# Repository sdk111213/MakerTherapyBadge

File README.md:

# MakerTherapyBadge
This repository is for the Electronics Pro Milestone at Purdue University for Spring 2021
This project will be a Maker therapy badge - a handheld electronic device that toggles through different settings for moods and even has an option for some games.

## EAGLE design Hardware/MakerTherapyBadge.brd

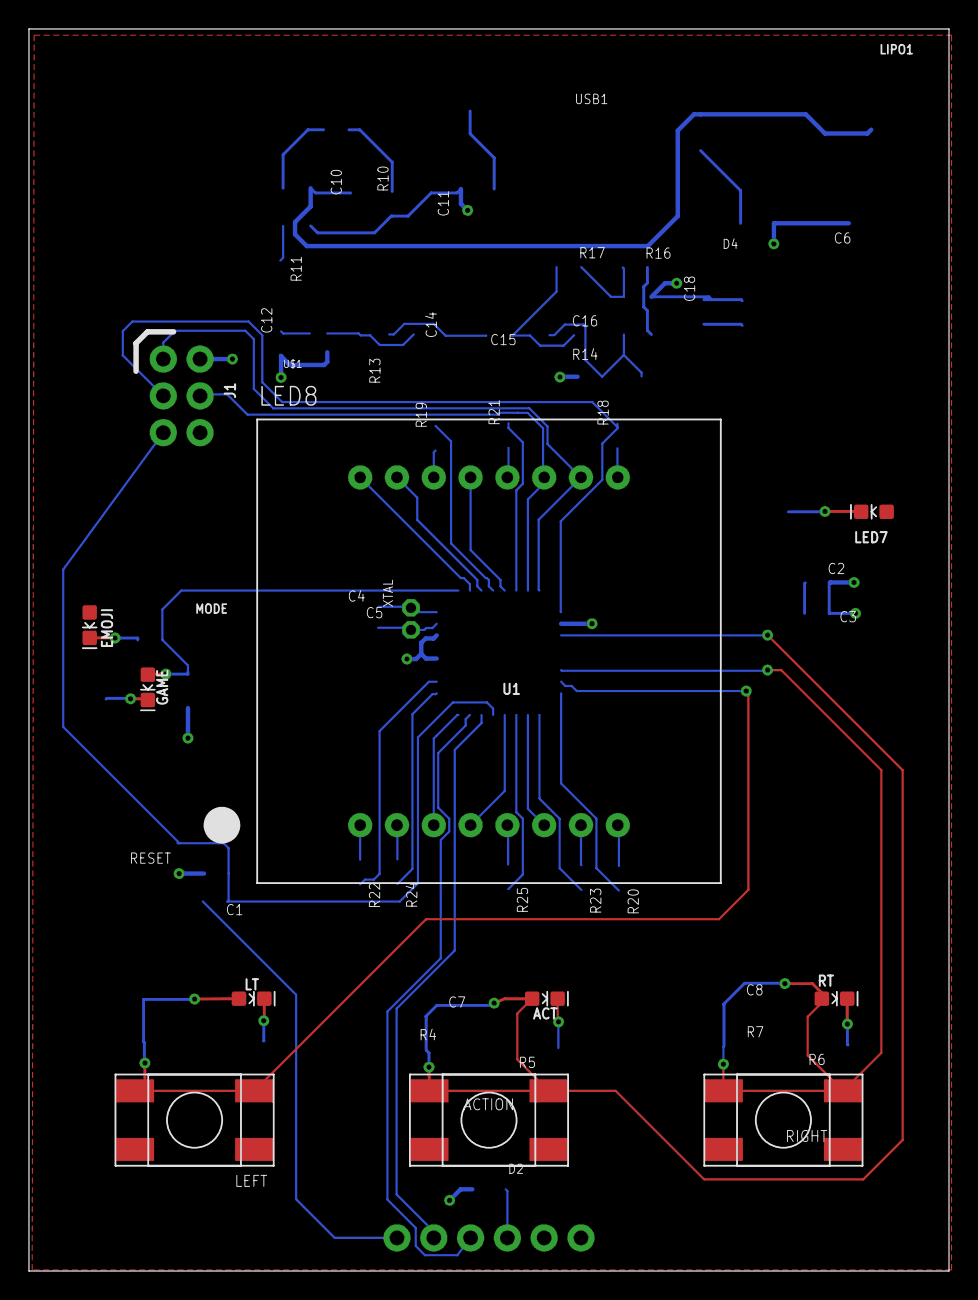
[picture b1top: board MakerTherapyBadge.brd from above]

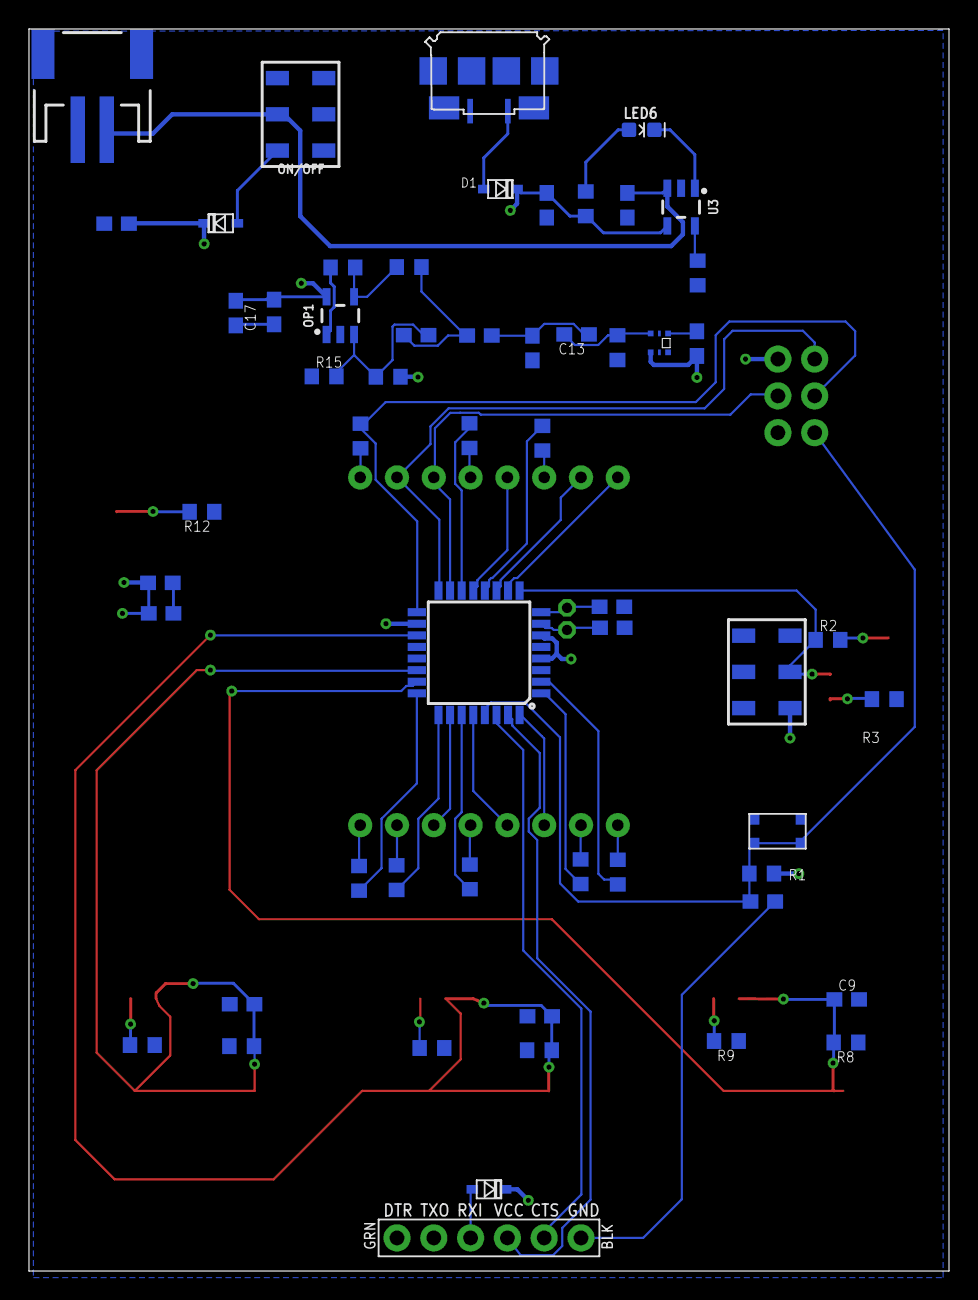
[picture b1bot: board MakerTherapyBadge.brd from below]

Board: 2 copper layers, 63.5 x 85.7 mm, 69 parts (57 on the bottom side), 55 nets.

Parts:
ACT: LED-0603
ACTION: SPST.KT11P4SM34LFS
C1, C3: 0.1u; C0603
C2, C16: 2.2u; C0603
C4, C5: 22p; C0603
C6, C10, C13, C14, C15: 4.7u; C0603
C7, C8, C9, C12, C17: 100n; C0603
C11: C0603
C18: 1u; C0603
D1, D4: 1A/23V/620mV; USC
D2: USC
EMOJI: LED-0603
FTDI1: FTDI_DEVICE
GAME: LED-0603
J1: AVR_SPI_PROG_3X2NS; 2X3-NS
LED6, LED7: LED-0603
LED8: SEGMENT_BL-M12A881UR
LEFT: SPST.KT11P4SM34LFS
LIPO1: JST-2-SMD
LT: LED-0603
MODE: SWITCH.JS202011JXQNUPWARDS; SWITCH.00
ON/OFF: SWITCH.JS202011JXQNUPWARDS; SWITCH.00
OP1: SOT23-5
R1, R4, R7, R8, R11, R17: 10k; R0603
R2, R3, R5, R6, R9, R10: 1k; R0603
R12: 487; R0603
R13: 12k; R0603
R14, R15: 210k; R0603
R16: 3.3M; R0603
R18, R19, R20, R21, R22, R23, R24, R25: 205; R0603
RESET: BUTTON-GULLWING
RIGHT: SPST.KT11P4SM34LFS
RT: LED-0603
U1: ATMEGA328P_TQFP; TQFP32-08
U3: MCP73831.SOT23-5; SOT23-5
U$1: ADPS9008; 6-PIN.CHIPLED
USB1: USB.MICRO.PWR-BIGGERPADS; USB-MICRO-01.BIGGERPADS.PWR
XTAL: CA-301

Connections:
ACTION: ACT.A, ACTION.3, ACTION.4, C7.2, R4.2, U1.19
DTR: C1.2, FTDI1.GND
GND: C2.2, C3.2, C4.2, C5.2, C6.2, C7.1, C8.1, C9.2, C10.2, C11.2, C12.1, C14.2, C17.2, C18.2, FTDI1.DTR, FTDI1.TXO, J1.6, LIPO1.1, MODE.1, OP1.2, R3.1, R4.1, R5.1, R6.1, R7.1, R8.1, R9.1, R11.1, R12.1, R13.1, R15.1, RESET.3, RESET.4, U1.3, U1.5, U1.21, U3.2, U$1.4, USB1.5
LD1: R22.1, U1.2
LD2: R24.1, U1.1
LD3: LED8.3, U1.32
LD4: LED8.4, U1.28
LD5: R25.1, U1.27
LD6: LED8.6, U1.26
LD7: R23.1, U1.25
LD8: R20.1, U1.24
LD9: J1.3, R18.1, U1.17
LD10: J1.1, LED8.10, U1.16
LD11: J1.4, LED8.11, U1.15
LD12: R21.1, U1.14
LD13: LED8.13, U1.13
LD14: R19.1, U1.12
LD15: LED8.15, U1.11
LD16: LED8.16, U1.10
LEFT: C9.1, LEFT.3, LEFT.4, LT.A, R8.2, U1.23
MODE: GAME.A, MODE.2, R2.1, U1.9
unnamed: LED8.9, R18.2
unnamed: D2.+, FTDI1.RXI
unnamed: LED8.14, R19.2
unnamed: LED8.8, R20.2
unnamed: LED8.12, R21.2
unnamed: C4.1, U1.8, XTAL.1
unnamed: D4.+, ON/OFF.1
unnamed: EMOJI.C, R2.2
unnamed: C5.1, U1.7, XTAL.2
unnamed: LT.C, R9.2
unnamed: LED8.1, R22.2
unnamed: LED8.7, R23.2
unnamed: LED8.2, R24.2
unnamed: GAME.C, R3.2
unnamed: ACT.C, R5.2
unnamed: R6.2, RT.C
unnamed: D1.+, USB1.1
unnamed: LED6.A, R10.1
unnamed: LED8.5, R25.2
unnamed: LED7.C, R12.2
unnamed: R11.2, U3.5
unnamed: OP1.4, R16.2, R17.1
unnamed: C16.2, OP1.3, R14.1, R15.2
unnamed: C13.2, R13.2, U$1.6
unnamed: C13.1, C14.1, C15.1
unnamed: C15.2, C16.1, R17.2
PULSE: OP1.1, R16.1
RESET: C1.1, J1.5, R1.2, RESET.1, RESET.2, U1.29
RIGHT: C8.2, R7.2, RIGHT.3, RIGHT.4, RT.A, U1.22
RXD: FTDI1.CTS, U1.30
STAT: LED6.C, U3.1
TXD: FTDI1.VCC, U1.31
VCC: ACTION.1, ACTION.2, C2.1, C3.1, C6.1, C11.1, C12.2, C17.1, C18.1, D1.-, D2.-, D4.-, EMOJI.A, J1.2, LED7.A, LEFT.1, LEFT.2, MODE.3, OP1.5, R1.1, R10.2, R14.2, RIGHT.1, RIGHT.2, U1.4, U1.6, U1.18, U3.4, U$1.1
VLIPO: C10.1, LIPO1.2, ON/OFF.2, U3.3

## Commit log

2021-02-20 Document of design choice answers
2021-02-20 renamed word file
2021-02-20 deleted file with wrong name
2021-02-20 document update
2021-02-20 new repository
2021-02-27 included sketch in word doc
2021-03-06 progress from march 6
2021-03-13 finished schematic
2021-03-13 partially worked on the board
2021-03-20 updates from 3/20
2021-03-20 slight new updates 3/20
2021-03-27 changes after 3/27
2021-03-27 small updates after recommendation
2021-04-03 updates after 4/3
2021-04-17 changes 4/17
2021-04-17 connected buttons
